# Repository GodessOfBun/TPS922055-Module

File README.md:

### If you find this project helpful please consider buying me coffee

</br>
</br>
This is a work in progress. The prototype has not confirmed to work or function well yet.
This module is designed with 48v VIN in mind, but can be used for  any voltages lower, the inductor can be calculated for every scenario using https://www.schemalyzer.com/en/tools/buck-converter-calculator.
Default operation frequency is 1.2Mhz but can be lowered to 600KHz for lower heat if space allows.
This design uses a 4 layer PCB which is very affordable at JLCPCB as long as the inner layers are 0.5oz. 

The module requires a 300uf~ bulk cap (perferrabily polymer) close to  VIN on the main PCB. Ensure the area under the module is grounded to reduce EMI if possible.

Silkscreen is removed over certain sections of ground to improve heat transfer. A heatsink will be required on the backside depending on the required load. Use a non-conductive thermal tape to adhere the heatsink to the PCB as the VCC and GND vias are both exposed on the backside. If not in use, cover with kapton tape. I have to figure out how to get KiCad to only cover the VCC vias...

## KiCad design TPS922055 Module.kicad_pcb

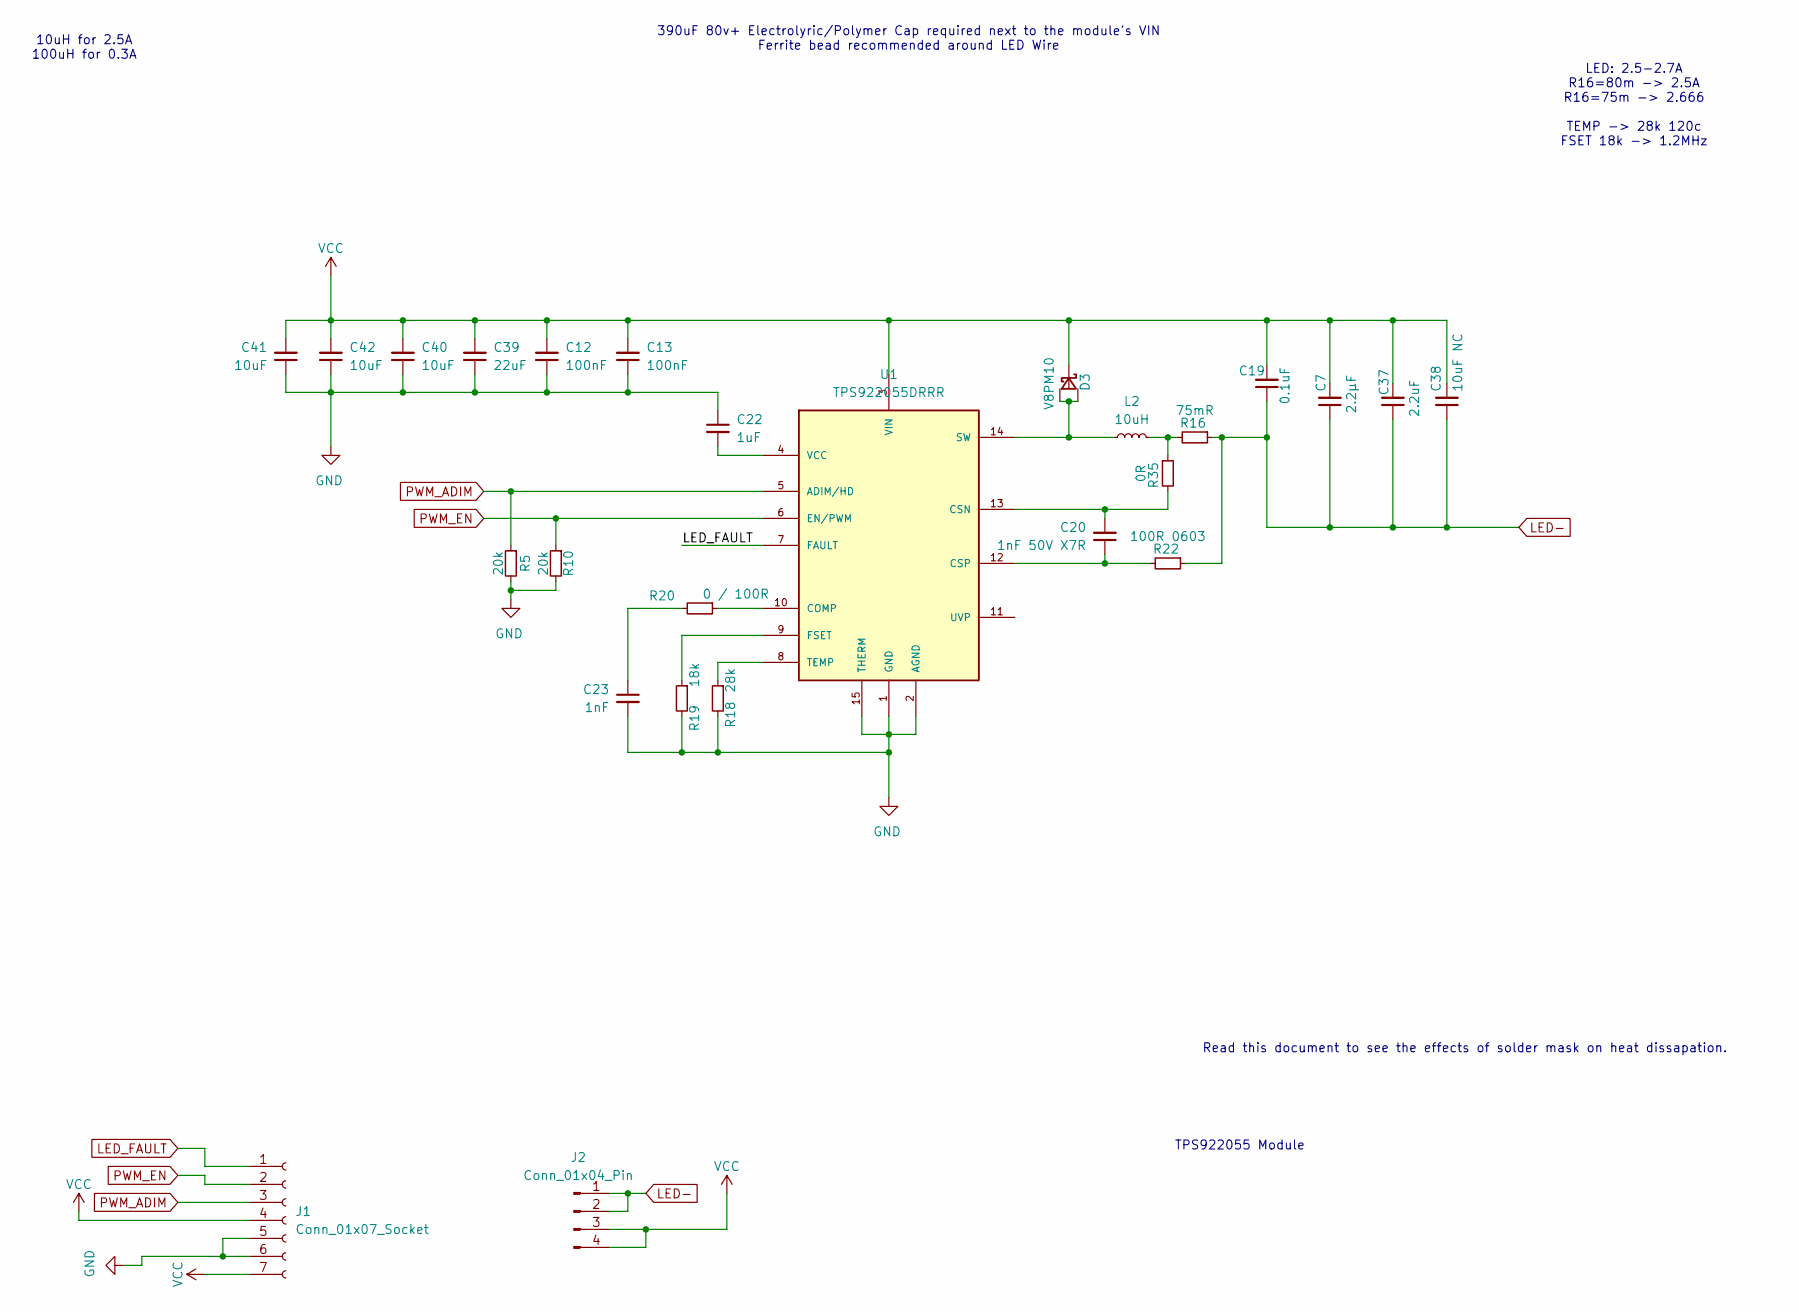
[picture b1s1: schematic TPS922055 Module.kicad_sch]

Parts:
C7: 2.2µF; C_1210_3225Metric
C12, C13: 100nF; C_0805_2012Metric
C19: 0.1uF; C_0805_2012Metric
C20: 1nF 50V X7R; C_0402_1005Metric
C22: 1uF; C_1206_3216Metric
C23: 1nF; C_0402_1005Metric
C37: 2.2uF; C_1210_3225Metric
C38: 10uF NC; C_1210_3225Metric
C39: 22uF; C_2220_5750Metric
C40, C41, C42: 10uF; C_1210_3225Metric
D3: V8PM10; TO-277A
J1: Conn_01x07_Socket; PinSocket_1x07_P2.54mm_Vertical
J2: Conn_01x04_Pin; PinSocket_1x04_P2.54mm_Vertical
L2: 10uH; L_Panasonic_PCC-M0754M
R5, R10: 20k; R_0603_1608Metric
R16: 75mR; R_2512_6332Metric
R18: 28k; R_0603_1608Metric
R19: 18k; R_0603_1608Metric
R20: 0 / 100R; R_0603_1608Metric
R22: 100R 0603; R_0603_1608Metric
R35: 0R; R_0603_1608Metric
U1: TPS922055DRRR; TPS922055DMTR; PARTREV A

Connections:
GND: C12.1, C13.1, C22.1, C23.2, C39.1, C40.1, C41.1, C42.1, J1.5, J1.6, R5.2, R10.2, R18.2, R19.2, U1.1 (GND), U1.2 (AGND), U1.15 (THERM)
LED-: C7.1, C19.1, C37.1, C38.1, J2.1, J2.2, R16.1, R22.1
LED_FAULT: J1.1, U1.7 (FAULT)
unnamed: C23.1, R20.2
unnamed: D3.1 (rA), D3.2 (A), L2.1, U1.14 (SW)
unnamed: L2.2, R16.2, R35.1
unnamed: R20.1, U1.10 (COMP)
unnamed: C20.2, R35.2, U1.13 (CSN)
unnamed: C20.1, R22.2, U1.12 (CSP)
unnamed: R19.1, U1.9 (FSET)
unnamed: R18.1, U1.8 (TEMP)
unnamed: C22.2, U1.4 (VCC)
PWM_ADIM: J1.3, R5.1, U1.5 (ADIM/HD)
PWM_EN: J1.2, R10.1, U1.6 (EN/PWM)
VCC: C7.2, C12.2, C13.2, C19.2, C37.2, C38.2, C39.2, C40.2, C41.2, C42.2, D3.3 (K), J1.4, J1.7, J2.3, J2.4, U1.3 (VIN)

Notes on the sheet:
Read this document to see the effects of solder mask on heat dissapation.
LED: 2.5-2.7A R16=80m -> 2.5A R16=75m -> 2.666 TEMP -> 28k 120c FSET 18k -> 1.2MHz
10uH for 2.5A 100uH for 0.3A
TPS922055 Module
390uF 80v+ Electrolyric/Polymer Cap required next to the module's VIN Ferrite bead recommended around LED Wire

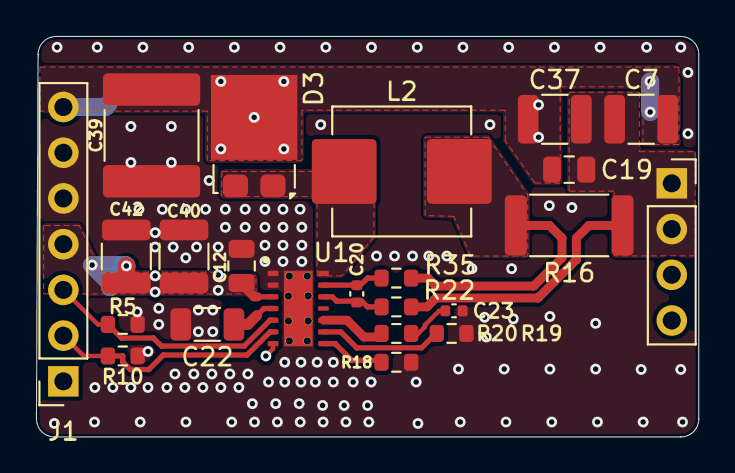
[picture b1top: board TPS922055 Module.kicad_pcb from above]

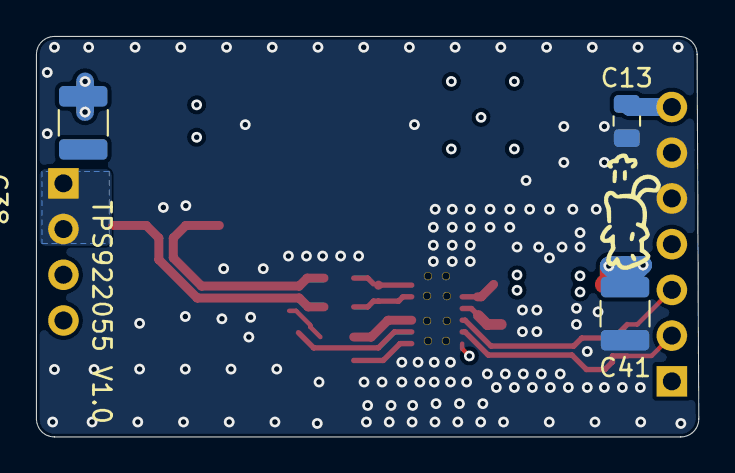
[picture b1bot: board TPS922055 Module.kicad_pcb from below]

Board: 4 copper layers, 36.8 x 22.2 mm, 26 parts (3 on the bottom side), 15 nets.

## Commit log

2026-04-14 initial
2026-04-19 Refinements, Increased module size to fit heatsink better
2026-04-19 Update README.md
    Fixed Ko-Fi link
